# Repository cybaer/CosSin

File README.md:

#CosSin 

a turntable power supply (TTPSU)

* suitable for Thorens TD14x/TD16x with 16V motors
* supplies a perfectly sinusoidal voltage
* electronic switching between 33 1/3 and 45 rpm
* fine adjustment for speed and phase position
* smooth start/brake and transition to another speed
* automatic switch-off after 25 or 15 minutes

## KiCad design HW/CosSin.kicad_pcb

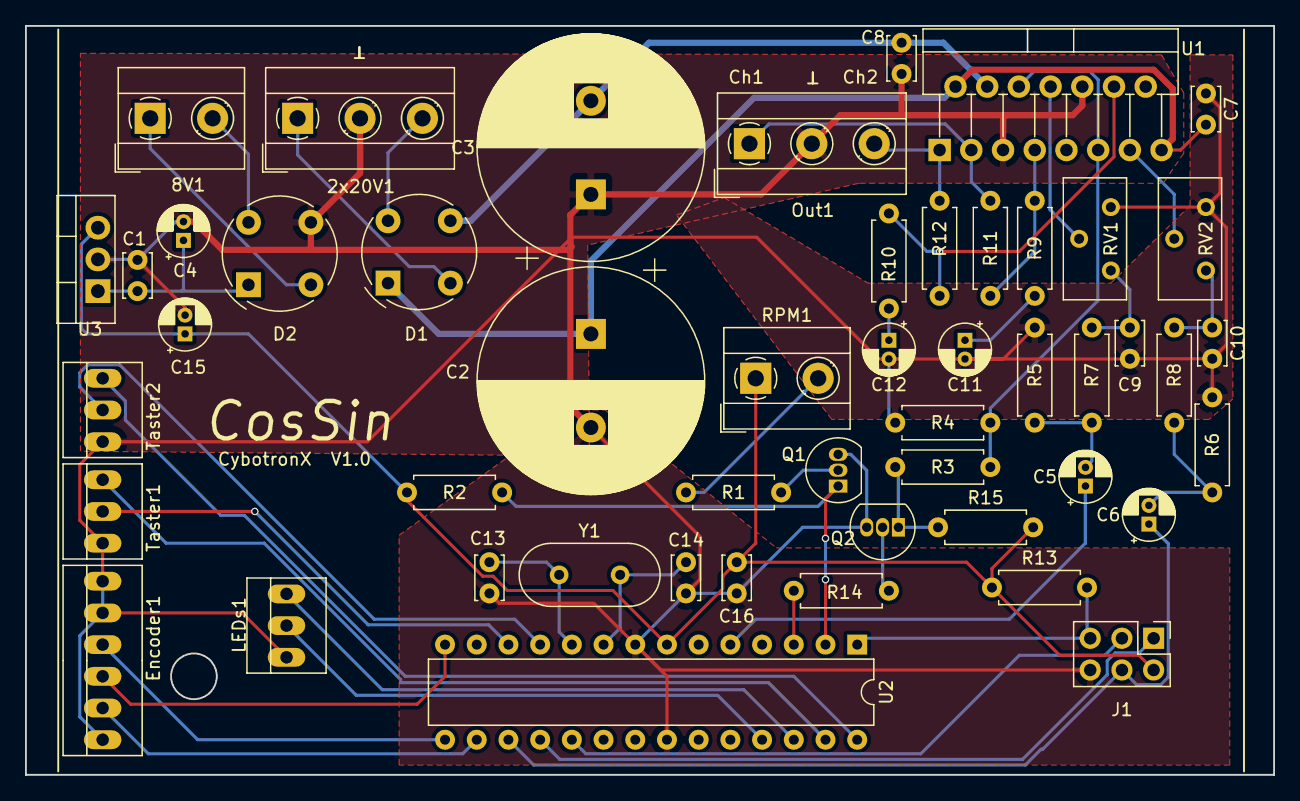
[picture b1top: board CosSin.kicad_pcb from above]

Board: 2 copper layers, 100.0 x 60.0 mm, 50 parts (0 on the bottom side), 44 nets.

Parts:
2x20V1: Screw_Terminal_01x03; TerminalBlock_MetzConnect_Type055_RT01503HDWU_1x03_P5.00mm_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
8V1: Screw_Terminal_01x02; TerminalBlock_MetzConnect_Type055_RT01502HDWU_1x02_P5.00mm_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
C1, C5, C6, C11, C12, C15: 10µ; CP_Radial_D4.0mm_P1.50mm
C2, C3: 2200µ/50V; CP_Radial_D18.0mm_P7.50mm
C4, C7, C8, C9, C10, C16: 100n; C_Disc_D3.4mm_W2.1mm_P2.50mm
C13, C14: 22p; C_Disc_D3.4mm_W2.1mm_P2.50mm
D1, D2: D_Bridge_+A-A; Diode_Bridge_Round_D9.0mm
Encoder1: Conn_01x06; PINHEAD1-6
J1: AVR-ISP-6; PinHeader_2x03_P2.54mm_Vertical
LEDs1: Conn_01x03; PINHEAD1-3
Out1: Screw_Terminal_01x03; TerminalBlock_MetzConnect_Type055_RT01503HDWU_1x03_P5.00mm_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
Q1, Q2: BC547; TO-92_Inline
R1, R4, R5, R6, R14: 100K; R_Axial_DIN0207_L6.3mm_D2.5mm_P7.62mm_Horizontal
R2, R7, R8, R13, R15: 10K; R_Axial_DIN0207_L6.3mm_D2.5mm_P7.62mm_Horizontal
R3, R9, R10: 1K; R_Axial_DIN0207_L6.3mm_D2.5mm_P7.62mm_Horizontal
R11, R12: 22K; R_Axial_DIN0207_L6.3mm_D2.5mm_P7.62mm_Horizontal
RPM1: Screw_Terminal_01x02; TerminalBlock_MetzConnect_Type055_RT01502HDWU_1x02_P5.00mm_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
RV1, RV2: 100K; Potentiometer_Bourns_3296Y_Vertical
Taster1, Taster2: Conn_01x03; PINHEAD1-3
U1: LM1876; TO-220-15_P2.54x2.54mm_StaggerOdd_Lead4.58mm_Vertical
U2: ATmega328P-PU; DIP-28_W7.62mm
U3: LM7805_TO220; TO-220-3_Vertical
Y1: Crystal; Crystal_HC49-U_Vertical

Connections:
+5V: C15.1, C16.1, J1.2, R2.2, R13.1, R15.2, RPM1.1, U2.7, U3.3
DDS2: C5.1, U2.5
ENC_A: Encoder1.2, U2.16
ENC_B: Encoder1.3, U2.14
ENC_S: Encoder1.4, U2.15
GND: 2x20V1.2, C1.2, C2.2, C3.1, C4.2, C7.2, C8.1, C9.2, C10.2, C11.2, C12.2, C13.2, C14.2, C15.2, C16.2, D2.3, Encoder1.1, Encoder1.5, Encoder1.6, J1.6, LEDs1.1, Out1.2, Q1.3, Q2.3, R4.2, R5.2, R6.2, RV1.3, RV2.3, Taster1.1, Taster2.1, U1.5, U1.10, U2.8, U2.22, U3.2
LED_1: Taster1.3, U2.27
LED_2: Taster2.3, U2.28
LED_3: LEDs1.3, U2.26
LED_4: LEDs1.2, U2.25
MISO: J1.1, U2.18
MOSI: C6.1, J1.4, U2.17
Mute: R3.1, R4.1, U1.6, U1.11
Mute_: R14.2, U2.3
unnamed: 2x20V1.1, D1.2
unnamed: 2x20V1.3, D1.4
unnamed: 8V1.1, D2.2
unnamed: 8V1.2, D2.4
unnamed: C1.1, C4.1, D2.1, U3.1
unnamed: C5.2, R5.1, R7.2
unnamed: C6.2, R6.1, R8.2
unnamed: C9.1, R7.1, RV1.1
unnamed: C10.1, R8.1, RV2.1
unnamed: C11.1, R9.2
unnamed: C12.1, R10.2
unnamed: C13.1, U2.10, Y1.1
unnamed: C14.1, U2.9, Y1.2
unnamed: Out1.1, R11.1, U1.3
unnamed: Out1.3, R12.1, U1.1
unnamed: Q1.2, R1.1
unnamed: Q2.1, R3.2, R15.1
unnamed: Q2.2, R14.1
unnamed: R1.2, RPM1.2
unnamed: R10.1, R12.2, U1.12
unnamed: R9.1, R11.2, U1.7
unnamed: RV1.2, U1.8
unnamed: RV2.2, U1.13
RPM: Q1.1, R2.1, U2.2
RST: J1.5, R13.2, U2.1
SCK: J1.3, U2.19
Tast_1: Taster1.2, U2.12
Tast_2: Taster2.2, U2.11
VCC: C2.1, C7.1, D1.1, U1.2, U1.15
VEE: C3.2, C8.2, D1.3, U1.4

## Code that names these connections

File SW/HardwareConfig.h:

#ifndef HARDWARECONFIG_H_
#define HARDWARECONFIG_H_

#include <avrlib/base.h>
#include <avrlib/gpio.h>
#include <avrlib/devices/rotary_encoder.h>

// __Compiler Bug__
__extension__ typedef int __guard __attribute__((mode (__DI__)));

extern "C" int __cxa_guard_acquire(__guard *);
extern "C" void __cxa_guard_release (__guard *);
extern "C" void __cxa_guard_abort (__guard *);
extern "C" void __cxa_pure_virtual();

using namespace avrlib;

typedef Inverter<Gpio<PortD, 1> > Mute;

typedef DebouncedSwitch< Gpio<PortD, 5> > Button_2;
typedef DebouncedSwitch< Gpio<PortD, 6> > Button_1;

typedef Gpio<PortB, 2> Encoder_A;
typedef Gpio<PortB, 0> Encoder_B;
typedef Gpio<PortB, 1> Encoder_S;
typedef RotaryEncoder<Encoder_A, Encoder_B, Encoder_S> Encoder;

typedef Gpio<PortC, 4> Led_1;
typedef Gpio<PortC, 5> Led_2;
typedef Gpio<PortC, 3> Led_3;
typedef Gpio<PortC, 2> Led_4;

inline void initOutputs()
{
  Mute::set_mode(DIGITAL_OUTPUT);
  Mute::High();
  Led_1::set_mode(DIGITAL_OUTPUT);
  Led_1::Low();
  Led_2::set_mode(DIGITAL_OUTPUT);
  Led_2::Low();
  Led_3::set_mode(DIGITAL_OUTPUT);
  Led_3::Low();
  Led_4::set_mode(DIGITAL_OUTPUT);
  Led_4::Low();
}

inline void initHW()
{
  initOutputs();

  Button_1::Init();
  Button_2::Init();
  Encoder::Init();
}

#endif

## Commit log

2023-02-16 new repo
2023-02-16 .gitignore added
2023-02-16 add avrlib as submodule
2023-02-17 state machine improved
2023-02-17 gitignore changed
2023-02-17 switch between 33 and 45 RPM possible
2023-03-02 Frequency and phase coarse adjustable
2023-06-05 PROGRAMMER_PORT added
2023-10-30 with SmartGenerator for smooth startup
2023-10-31 Start sequence improved, beautifying
2023-11-03 Startup sequence fine tuning
2023-11-08 RPM data storage at EEPROM, some improvements
2023-11-21 start problems without programmer cleared, beautifying
2023-11-22 automatic stopp implemented
2023-11-26 Auto stop switchable some beautifying
